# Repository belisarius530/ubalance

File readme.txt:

This is the first of many files,
may they all be merry and bright -JF

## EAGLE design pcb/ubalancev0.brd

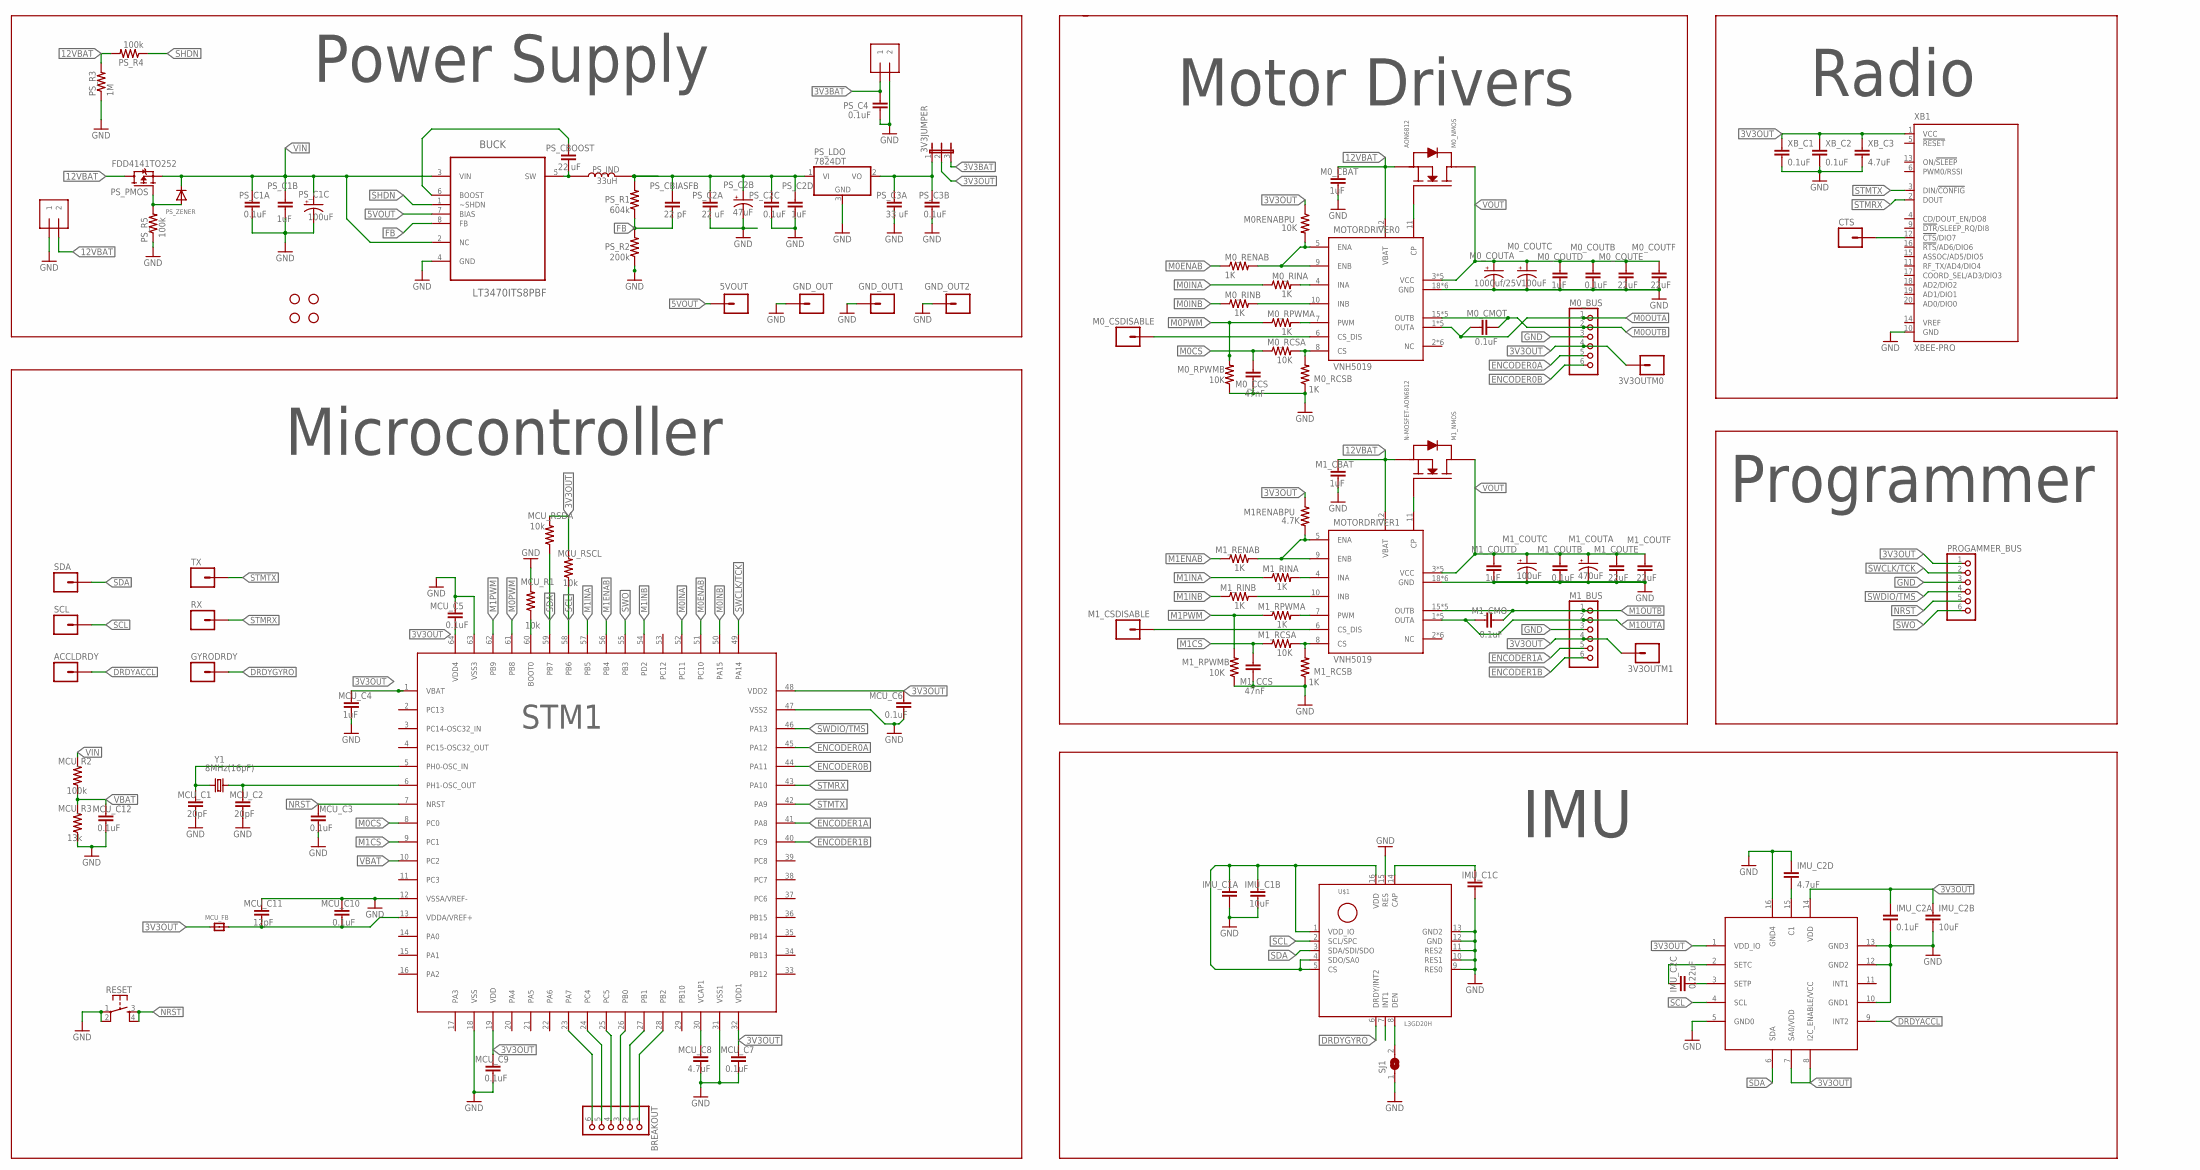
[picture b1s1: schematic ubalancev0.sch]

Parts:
3V3JUMPER: JUMPER3
3V3OUTM0, 3V3OUTM1, 5VOUT: M01PTH; 1X01
ACCLDRDY: M01PTH; 1X01
BREAKOUT: PINHD-1X6LOCK; 1X06-BIGLOCK
BUCK: LT3470ITS8PBF; SOT65P280X100-8N
CTS: M01PTH; 1X01
GND_OUT, GND_OUT1, GND_OUT2: M01PTH; 1X01
GYRODRDY: M01PTH; 1X01
IMU_C1A, IMU_C2A: 0.1uF; 0805
IMU_C1B, IMU_C2B: 10uF; 0805
IMU_C1C: 10nF; 0805
IMU_C2C: 0.22uF; 0805
IMU_C2D: 4.7uF; 0805
M0RENABPU, M0_RCSA, M0_RPWMB, M1_RCSA, M1_RPWMB: 10K; 0805
M0_BUS, M1_BUS: PINHD-1X6LOCK; 1X06-BIGLOCK
M0_CBAT, M0_COUTD, M1_CBAT, M1_COUTD: 1uF; 0805
M0_CCS, M1_CCS: 47nF; 0805
M0_CMOT, M0_COUTB, M1_CMO, M1_COUTB: 0.1uF; 0805
M0_COUTA: 1000uf/25V; CPOL-RADIAL-1000UF-25V-KIT
M0_COUTC, M1_COUTC: 100uF; PANASONIC_D
M0_COUTE, M1_COUTE, M1_COUTF: 22uF; 1206
M0_COUTF: 22uF; 0805
M0_CSDISABLE, M1_CSDISABLE: M01PTH; 1X01
M0_NMOS: AON6812; 8DFN-5*6MM
M0_RCSB, M0_RENAB, M0_RINA, M0_RINB, M0_RPWMA, M1_RCSB, M1_RENAB, M1_RINA, M1_RINB, M1_RPWMA: 1K; 0805
M1RENABPU: 4.7K; 0805
M1_COUTA: 470uF; PANASONIC_G
M1_NMOS: N-MOSFET-AON6812; 8DFN-5*6MM
MCU_C1, MCU_C2: 20pF; 0805
MCU_C3, MCU_C5, MCU_C6, MCU_C7, MCU_C9, MCU_C10, MCU_C12: 0.1uF; 0805
MCU_C4: 1uF; 0805
MCU_C8: 4.7uF; 0805
MCU_C11: 12pF; 0805
MCU_FB: FERRITE; 0603
MCU_R1: 10k; 0805
MCU_R2: 100k; 0805
MCU_R3: 13k; 0805
MCU_RSCL: 10k; 0805
MCU_RSDA: 10k; 0805
MOTORDRIVER0, MOTORDRIVER1: VNH5019; MULTIPOWERSO-30
PROGAMMER_BUS: PINHD-1X6LOCK; 1X06-BIGLOCK
PS_3V3TERM, PS_12VTERM: 1X2-3.5MM
PS_C1A, PS_C2C, PS_C3B, PS_C4: 0.1uF; 0805
PS_C1B, PS_C2D: 1uF; 0805
PS_C1C: 100uF; PANASONIC_D
PS_C2A: 22 uF; 1206
PS_C2B: 47uF; PANASONIC_D
PS_C3A: 33 uF; 1206
PS_CBIASFB: 22 pF; 0805
PS_CBOOST: .22 uF; 0402-CAP
PS_IND: 33uH; VLCF5024
PS_LDO: 7824DT; TO252
PS_PMOS: FDD4141TO252; TO252
PS_R1: 604k; 0805
PS_R2: 200k; 0805
PS_R3: 1M; 0805
PS_R4, PS_R5: 100k; 0805
PS_ZENER: DIODESOD-123; SOD-123
RESET: TAC_SWITCHPTH; TACTILE-PTH
RX: M01PTH; 1X01
SCL: M01PTH; 1X01
SDA: M01PTH; 1X01
SJ1: SOLDERJUMPER; SOLDERJUMPER_ARROW_NOPASTE
STANDOFF1, STANDOFF2, STANDOFF3, STANDOFF4: STAND-OFF
STM1: STM32F4; LQFP64
TX: M01PTH; 1X01
U$1: L3GD20H; LGA16_3X3MM
U$2: LSM303D; LGA16_3X3MM
XB1: XBEE-PRO
XB_C1, XB_C2: 0.1uF; 0805
XB_C3: 4.7uF; 0805
Y1: 8MHz(16pF); HC49US

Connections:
3V3BAT: 3V3JUMPER.3, PS_3V3TERM.1, PS_C4.1
3V3OUT: 3V3JUMPER.2, 3V3OUTM0.1, 3V3OUTM1.1, IMU_C1A.1, IMU_C1B.1, IMU_C2A.1, IMU_C2B.1, M0RENABPU.1, M0_BUS.4, M1RENABPU.1, M1_BUS.4, MCU_C4.1, MCU_C5.1, MCU_C6.2, MCU_C7.1, MCU_C9.1, MCU_FB.1, MCU_RSCL.2, MCU_RSDA.2, PROGAMMER_BUS.1, STM1.1 (VBAT), STM1.19 (VDD), STM1.32 (VDD1), STM1.48 (VDD2), STM1.64 (VDD4), U$1.1 (VDD_IO), U$1.4 (SDO/SA0), U$1.5 (CS), U$1.16 (VDD), U$2.1 (VDD_IO), U$2.7 (SA0/VDD), U$2.8 (I2C_ENABLE/VCC), U$2.14 (VDD), XB1.1 (VCC), XB_C1.1, XB_C2.1, XB_C3.1
3V3OUTREG: 3V3JUMPER.1, PS_C3A.1, PS_C3B.1, PS_LDO.2 (VO)
5VOUT: 5VOUT.1, BUCK.7 (BIAS), PS_C2A.1, PS_C2B.+, PS_C2C.1, PS_C2D.1, PS_CBIASFB.1, PS_IND.P2, PS_LDO.1 (VI), PS_R1.2
12VBAT: M0_CBAT.1, M0_NMOS.S1 (SOURCE), M0_NMOS.S2 (SOURCE), M0_NMOS.S3 (SOURCE), M1_CBAT.1, M1_NMOS.S1 (SOURCE), M1_NMOS.S2 (SOURCE), M1_NMOS.S3 (SOURCE), MOTORDRIVER0.12 (VBAT), MOTORDRIVER1.12 (VBAT), PS_12VTERM.2, PS_PMOS.3 (D), PS_R3.2, PS_R4.2
CAP: IMU_C1C.1, U$1.14 (CAP)
DRDYACCL: ACCLDRDY.1, U$2.9 (INT2)
DRDYGYRO: GYRODRDY.1, U$1.6 (DRDY/INT2)
ENCODER0A: M0_BUS.5, STM1.45 (PA12)
ENCODER0B: M0_BUS.6, STM1.44 (PA11)
ENCODER1A: M1_BUS.5, STM1.41 (PA8)
ENCODER1B: M1_BUS.6, STM1.40 (PC9)
FB: BUCK.8 (FB), PS_CBIASFB.2, PS_R1.1, PS_R2.2
GND: BUCK.4 (GND), GND_OUT.1, GND_OUT1.1, GND_OUT2.1, IMU_C1A.2, IMU_C1B.2, IMU_C1C.2, IMU_C2A.2, IMU_C2B.2, IMU_C2D.1, M0_BUS.3, M0_CBAT.2, M0_CCS.2, M0_COUTA.-, M0_COUTB.2, M0_COUTC.-, M0_COUTD.2, M0_COUTE.2, M0_COUTF.2, M0_RCSB.1, M0_RPWMB.1, M1_BUS.3, M1_CBAT.2, M1_CCS.2, M1_COUTA.-, M1_COUTB.2, M1_COUTC.-, M1_COUTD.2, M1_COUTE.2, M1_COUTF.2, M1_RCSB.1, M1_RPWMB.1, MCU_C1.2, MCU_C2.2, MCU_C3.2, MCU_C4.2, MCU_C5.2, MCU_C6.1, MCU_C7.2, MCU_C8.2, MCU_C9.2, MCU_C10.2, MCU_C11.1, MCU_C12.2, MCU_R1.2, MCU_R3.1, MOTORDRIVER0.18 (GND), MOTORDRIVER0.19 (GND), MOTORDRIVER0.20 (GND), MOTORDRIVER0.26 (GND), MOTORDRIVER0.27 (GND), MOTORDRIVER0.28 (GND), MOTORDRIVER1.18 (GND), MOTORDRIVER1.19 (GND), MOTORDRIVER1.20 (GND), MOTORDRIVER1.26 (GND), MOTORDRIVER1.27 (GND), MOTORDRIVER1.28 (GND), PROGAMMER_BUS.3, PS_3V3TERM.2, PS_12VTERM.1, PS_C1A.2, PS_C1B.2, PS_C1C.-, PS_C2A.2, PS_C2B.-, PS_C2C.2, PS_C2D.2, PS_C3A.2, PS_C3B.2, PS_C4.2, PS_LDO.3 (GND), PS_R2.1, PS_R3.1, PS_R5.1, RESET.1, RESET.2, SJ1.1, STM1.12 (VSSA/VREF-), STM1.18 (VSS), STM1.31 (VSS1), STM1.47 (VSS2), STM1.63 (VSS3), U$1.9 (RES0), U$1.10 (RES1), U$1.11 (RES2), U$1.12 (GND), U$1.13 (GND2), U$1.15 (RES), U$2.5 (GND0), U$2.10 (GND1), U$2.12 (GND2), U$2.13 (GND3), U$2.16 (GND4), XB1.10 (GND), XB_C1.2, XB_C2.2, XB_C3.2
M0CS: M0_CCS.1, M0_RCSA.1, STM1.8 (PC0)
M0ENAB: M0_RENAB.1, STM1.51 (PC10)
M0INA: M0_RINA.1, STM1.52 (PC11)
M0INB: M0_RINB.1, STM1.50 (PA15)
M0OUTA: M0_BUS.1, M0_CMOT.1, MOTORDRIVER0.1 (OUTA), MOTORDRIVER0.25 (OUTA), MOTORDRIVER0.30 (OUTA), MOTORDRIVER0.OUTA, MOTORDRIVER0.OUTA@1 (OUTA)
M0OUTB: M0_BUS.2, M0_CMOT.2, MOTORDRIVER0.15 (OUTB), MOTORDRIVER0.16 (OUTB), MOTORDRIVER0.21 (OUTB), MOTORDRIVER0.OUTB, MOTORDRIVER0.OUTB@1 (OUTB)
M0PWM: M0_RPWMA.1, M0_RPWMB.2, STM1.61 (PB8)
M1CS: M1_CCS.1, M1_RCSA.1, STM1.9 (PC1)
M1ENAB: M1_RENAB.1, STM1.56 (PB4)
M1INA: M1_RINA.1, STM1.57 (PB5)
M1INB: M1_RINB.1, STM1.54 (PD2)
M1OUTA: M1_BUS.2, M1_CMO.1, MOTORDRIVER1.1 (OUTA), MOTORDRIVER1.25 (OUTA), MOTORDRIVER1.30 (OUTA), MOTORDRIVER1.OUTA, MOTORDRIVER1.OUTA@1 (OUTA)
M1OUTB: M1_BUS.1, M1_CMO.2, MOTORDRIVER1.15 (OUTB), MOTORDRIVER1.16 (OUTB), MOTORDRIVER1.21 (OUTB), MOTORDRIVER1.OUTB, MOTORDRIVER1.OUTB@1 (OUTB)
M1PWM: M1_RPWMA.1, M1_RPWMB.2, STM1.62 (PB9)
unnamed: M1_NMOS.G (GATE), MOTORDRIVER1.11 (CP)
unnamed: BUCK.6 (BOOST), PS_CBOOST.1
unnamed: M0_NMOS.G (GATE), MOTORDRIVER0.11 (CP)
unnamed: IMU_C2C.1, U$2.3 (SETP)
unnamed: BREAKOUT.6, STM1.23 (PA7)
unnamed: M0RENABPU.2, M0_RENAB.2, MOTORDRIVER0.5 (ENA), MOTORDRIVER0.9 (ENB)
unnamed: MCU_C10.1, MCU_C11.2, MCU_FB.2, STM1.13 (VDDA/VREF+)
unnamed: BREAKOUT.5, STM1.24 (PC4)
unnamed: M0_RINA.2, MOTORDRIVER0.4 (INA)
unnamed: M0_RINB.2, MOTORDRIVER0.10 (INB)
unnamed: M0_RPWMA.2, MOTORDRIVER0.7 (PWM)
unnamed: M0_CSDISABLE.1, MOTORDRIVER0.6 (CS_DIS)
unnamed: M0_RCSA.2, M0_RCSB.2, MOTORDRIVER0.8 (CS)
unnamed: MCU_C8.1, STM1.30 (VCAP1)
unnamed: MCU_R1.1, STM1.60 (BOOT0)
unnamed: IMU_C2D.2, U$2.15 (C1)
unnamed: IMU_C2C.2, U$2.2 (SETC)
unnamed: BREAKOUT.4, STM1.25 (PC5)
unnamed: M1RENABPU.2, M1_RENAB.2, MOTORDRIVER1.5 (ENA), MOTORDRIVER1.9 (ENB)
unnamed: M1_RINA.2, MOTORDRIVER1.4 (INA)
unnamed: M1_RINB.2, MOTORDRIVER1.10 (INB)
unnamed: M1_RPWMA.2, MOTORDRIVER1.7 (PWM)
unnamed: M1_CSDISABLE.1, MOTORDRIVER1.6 (CS_DIS)
unnamed: M1_RCSA.2, M1_RCSB.2, MOTORDRIVER1.8 (CS)
unnamed: BREAKOUT.3, STM1.26 (PB0)
unnamed: MCU_C1.1, STM1.5 (PH0-OSC_IN), Y1.1
unnamed: MCU_C2.1, STM1.6 (PH1-OSC_OUT), Y1.2
unnamed: BREAKOUT.2, STM1.27 (PB1)
unnamed: BREAKOUT.1, STM1.28 (PB2)
unnamed: SJ1.2, U$1.8 (DEN)
unnamed: CTS.1, XB1.12 (!CTS!/DIO7)
NRST: MCU_C3.1, PROGAMMER_BUS.5, RESET.3, RESET.4, STM1.7 (NRST)
PMOSGATE: PS_PMOS.1 (G), PS_R5.2, PS_ZENER.A
SCL: MCU_RSCL.1, SCL.1, STM1.58 (PB6), U$1.2 (SCL/SPC), U$2.4 (SCL)
SDA: MCU_RSDA.1, SDA.1, STM1.59 (PB7), U$1.3 (SDA/SDI/SDO), U$2.6 (SDA)
SHDN: BUCK.1 (~SHDN), PS_R4.1
STMRX: RX.1, STM1.43 (PA10), XB1.2 (DOUT)
STMTX: STM1.42 (PA9), TX.1, XB1.3 (DIN/!CONFIG)
SW: BUCK.5 (SW), PS_CBOOST.2, PS_IND.P1
SWCLK/TCK: PROGAMMER_BUS.2, STM1.49 (PA14)
SWDIO/TMS: PROGAMMER_BUS.4, STM1.46 (PA13)
SWO: PROGAMMER_BUS.6, STM1.55 (PB3)
VBAT: MCU_C12.1, MCU_R2.1, MCU_R3.2, STM1.10 (PC2)
VIN: BUCK.2 (NC), BUCK.3 (VIN), MCU_R2.2, PS_C1A.1, PS_C1B.1, PS_C1C.+, PS_PMOS.2 (S), PS_ZENER.C
VOUT: M0_COUTA.+, M0_COUTB.1, M0_COUTC.+, M0_COUTD.1, M0_COUTE.1, M0_COUTF.1, M0_NMOS.D1 (DRAIN), M0_NMOS.D2 (DRAIN), M0_NMOS.D3 (DRAIN), M0_NMOS.D4 (DRAIN), M0_NMOS.D5 (DRAIN), M1_COUTA.+, M1_COUTB.1, M1_COUTC.+, M1_COUTD.1, M1_COUTE.1, M1_COUTF.1, M1_NMOS.D1 (DRAIN), M1_NMOS.D2 (DRAIN), M1_NMOS.D3 (DRAIN), M1_NMOS.D4 (DRAIN), M1_NMOS.D5 (DRAIN), MOTORDRIVER0.3 (VCC), MOTORDRIVER0.13 (VCC), MOTORDRIVER0.23 (VCC), MOTORDRIVER0.VCC, MOTORDRIVER0.VCC@1 (VCC), MOTORDRIVER1.3 (VCC), MOTORDRIVER1.13 (VCC), MOTORDRIVER1.23 (VCC), MOTORDRIVER1.VCC, MOTORDRIVER1.VCC@1 (VCC)

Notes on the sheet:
Microcontroller
Power Supply
Motor Drivers
Radio
IMU
Programmer

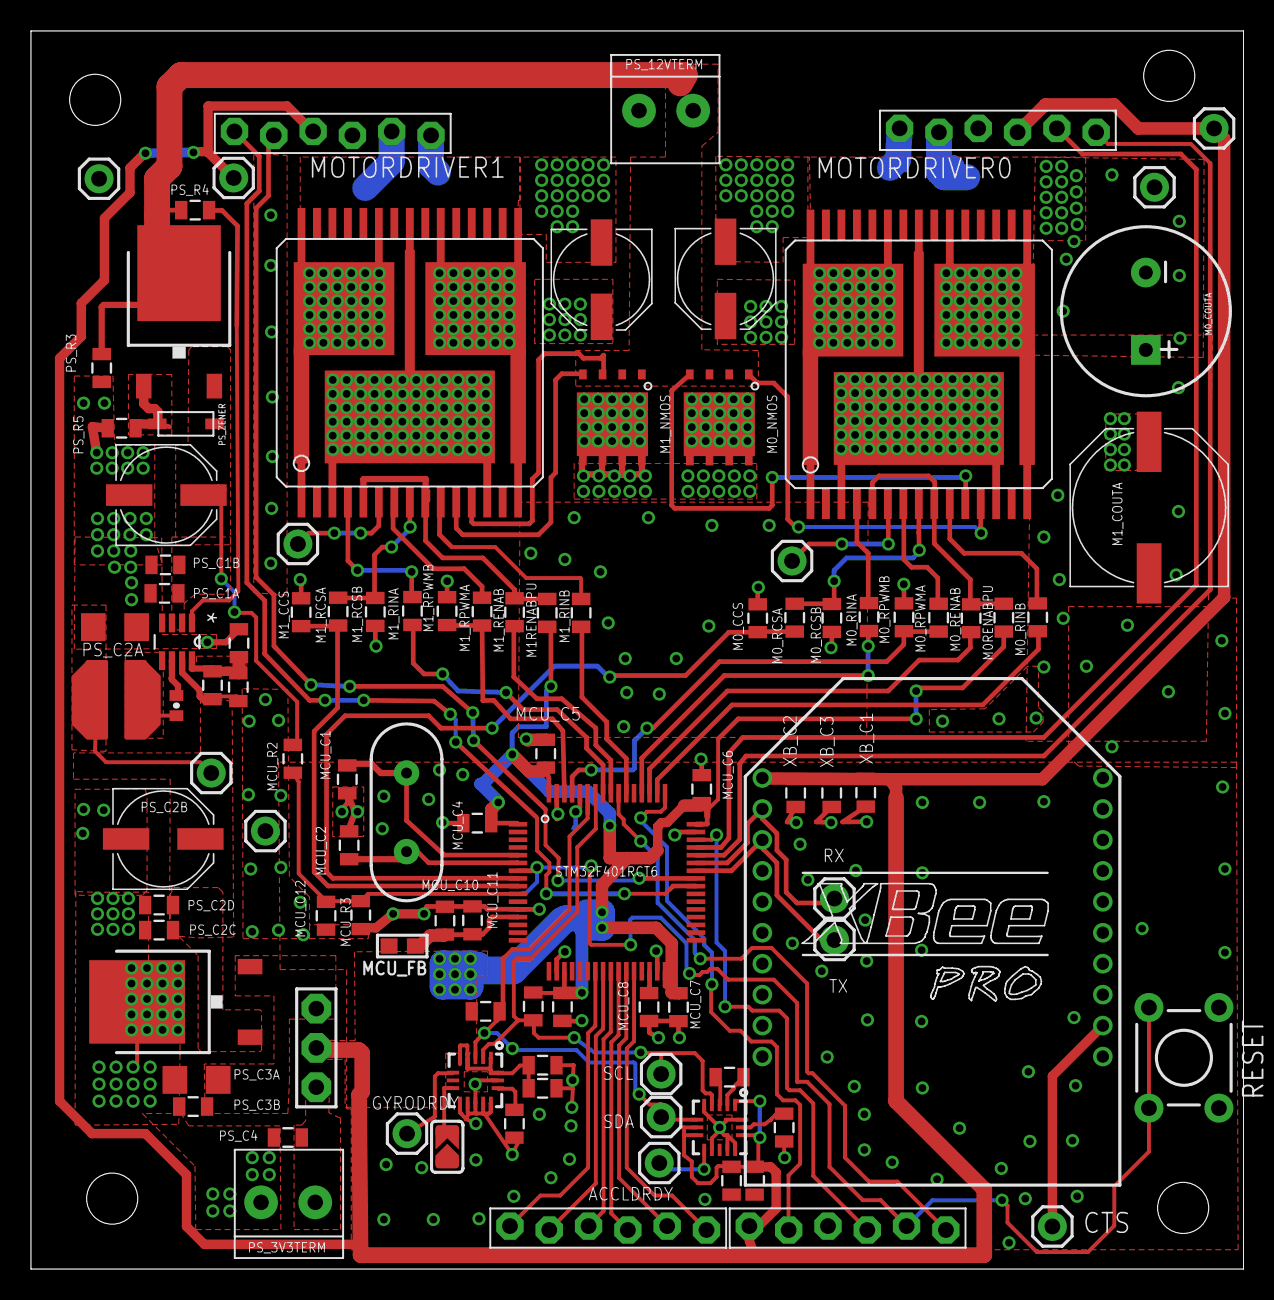
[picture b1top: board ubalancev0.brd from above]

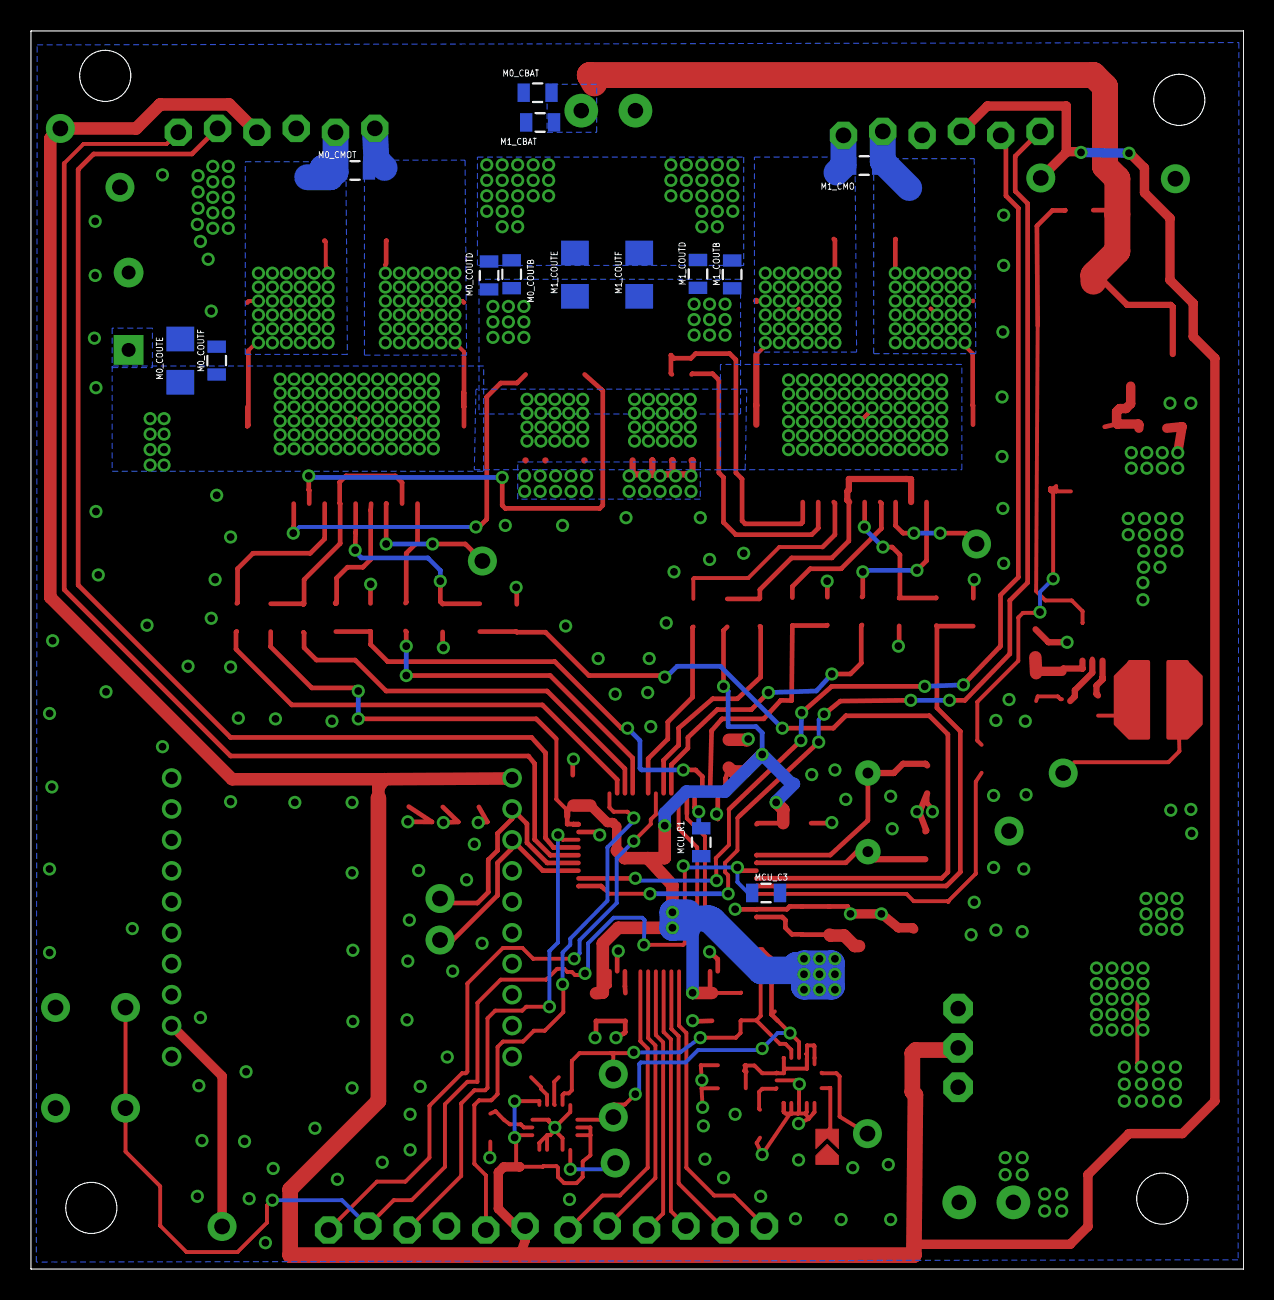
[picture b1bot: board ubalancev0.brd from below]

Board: 2 copper layers, 78.3 x 80.0 mm, 121 parts (14 on the bottom side), 73 nets.

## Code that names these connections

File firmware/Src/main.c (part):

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  __GPIOA_CLK_ENABLE();
  __GPIOB_CLK_ENABLE();

    /*Configure GPIO pins : PC9(ENCODER1B) */
    GPIO_InitStruct.Pin = GPIO_PIN_9;
    GPIO_InitStruct.Mode = GPIO_MODE_IT_RISING_FALLING;
    GPIO_InitStruct.Pull = GPIO_NOPULL;
    HAL_GPIO_Init(GPIOC, &GPIO_InitStruct);
        
    /*Configure GPIO pins : PA8(ENCODER1A) */
    GPIO_InitStruct.Pin = GPIO_PIN_8;
    GPIO_InitStruct.Mode = GPIO_MODE_IT_RISING_FALLING;
    GPIO_InitStruct.Pull = GPIO_NOPULL;
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    HAL_NVIC_SetPriority(EXTI9_5_IRQn, 5, 0);
    HAL_NVIC_EnableIRQ(EXTI9_5_IRQn);
    
    /*Configure GPIO pins : PA11(ENCODER0B), PA12(ENCODER0A) */
    GPIO_InitStruct.Pin = GPIO_PIN_11|GPIO_PIN_12;
    GPIO_InitStruct.Mode = GPIO_MODE_IT_RISING_FALLING;
    GPIO_InitStruct.Pull = GPIO_NOPULL;
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  GPIO_InitStruct.Alternate = GPIO_AF7_USART2;
  HAL_GPIO_Init(GPIOA, &GPIO_InitStruct);

  /*Configure GPIO pin : PA5(LED), PA15(M0INB) */
  GPIO_InitStruct.Pin = GPIO_PIN_5|GPIO_PIN_15;
  GPIO_InitStruct.Mode = GPIO_MODE_OUTPUT_PP;
  GPIO_InitStruct.Pull = GPIO_NOPULL;
  GPIO_InitStruct.Speed = GPIO_SPEED_LOW;
  HAL_GPIO_Init(GPIOA, &GPIO_InitStruct);
  
  /*Configure GPIO pins : PC10(M0ENAB) */
  GPIO_InitStruct.Pin = GPIO_PIN_10;
  GPIO_InitStruct.Mode = GPIO_MODE_INPUT;
  GPIO_InitStruct.Pull = GPIO_PULLUP;
  HAL_GPIO_Init(GPIOC, &GPIO_InitStruct);
  
  /*Configure GPIO pins : PC11(M0INA) */
  GPIO_InitStruct.Pin = GPIO_PIN_11;
  GPIO_InitStruct.Mode = GPIO_MODE_OUTPUT_PP;
  GPIO_InitStruct.Pull = GPIO_NOPULL;
  GPIO_InitStruct.Speed = GPIO_SPEED_LOW;
  HAL_GPIO_Init(GPIOC, &GPIO_InitStruct);
  
  /*Configure GPIO pins : PD2(M1INB) */
  GPIO_InitStruct.Pin = GPIO_PIN_2;
  GPIO_InitStruct.Mode = GPIO_MODE_OUTPUT_PP;
  GPIO_InitStruct.Pull = GPIO_NOPULL;
  GPIO_InitStruct.Speed = GPIO_SPEED_LOW;
  HAL_GPIO_Init(GPIOD, &GPIO_InitStruct);

  /*Configure GPIO pins : PB4(M1ENAB) */
  GPIO_InitStruct.Pin = GPIO_PIN_4;
  GPIO_InitStruct.Mode = GPIO_MODE_INPUT;
  GPIO_InitStruct.Pull = GPIO_PULLUP;
  HAL_GPIO_Init(GPIOB, &GPIO_InitStruct);
  
  /*Configure GPIO pins : PB5(M1INA) */
  GPIO_InitStruct.Pin = GPIO_PIN_5;
  GPIO_InitStruct.Mode = GPIO_MODE_OUTPUT_PP;
  GPIO_InitStruct.Pull = GPIO_NOPULL;
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
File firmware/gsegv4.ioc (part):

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Mcu.Name=STM32F401R(B-C-D-E)Tx
Mcu.Package=LQFP64
Mcu.UserName=STM32F401RETx
PA10.Mode=Asynchronous
PA10.Signal=USART1_RX
PA13.GPIOParameters=GPIO_Label
PA13.GPIO_Label=TMS
PA13.Mode=Trace-Asynchronous_SW
PA13.Signal=SYS_JTMS-SWDIO
PA14.GPIOParameters=GPIO_Label
PA14.GPIO_Label=TCK
PA14.Mode=Trace-Asynchronous_SW
PA14.Signal=SYS_JTCK-SWCLK
PA2.GPIOParameters=GPIO_Label,GPIO_Speed,GPIO_PuPd,GPIO_Mode
PA2.GPIO_Label=USART_TX
PA2.GPIO_Mode=GPIO_MODE_AF_PP
PA2.GPIO_PuPd=GPIO_NOPULL
PA2.GPIO_Speed=GPIO_SPEED_LOW
PA2.Signal=USART2_TX
PA3.GPIOParameters=GPIO_Label,GPIO_Speed,GPIO_PuPd,GPIO_Mode
PA3.GPIO_Label=USART_RX
PA3.GPIO_Mode=GPIO_MODE_AF_PP
PA3.GPIO_PuPd=GPIO_NOPULL
PA3.GPIO_Speed=GPIO_SPEED_LOW
PA3.Signal=USART2_RX
PA5.GPIOParameters=GPIO_ModeDefaultOutputPP,GPIO_Label,GPIO_Speed,GPIO_PuPd,GPIO_Mode
PA5.GPIO_Label=LD2 [Green Led]
PA5.GPIO_Mode=GPIO_MODE_OUTPUT_PP
PA5.GPIO_ModeDefaultOutputPP=GPIO_MODE_OUTPUT_PP
PA5.GPIO_PuPd=GPIO_NOPULL
PA5.GPIO_Speed=GPIO_SPEED_LOW
PA5.Signal=GPIO_Output
PA9.Mode=Asynchronous
PA9.Signal=USART1_TX
PB3.GPIOParameters=GPIO_Label
PB3.GPIO_Label=SWO
PB3.Mode=Trace-Asynchronous_SW
PB3.Signal=SYS_JTDO-SWO
PB6.Mode=I2C
PB6.Signal=I2C1_SCL
PB7.Mode=I2C
PB7.Signal=I2C1_SDA
PB8.Signal=S_TIM10_CH1
PB9.Signal=S_TIM11_CH1
PC0.Signal=ADCx_IN10
PC1.Signal=ADCx_IN11
PC13-ANTI_TAMP.GPIOParameters=GPIO_Label,GPIO_ModeDefaultEXTI,GPIO_PuPd
PC13-ANTI_TAMP.GPIO_Label=B1 [Blue PushButton]
PC13-ANTI_TAMP.GPIO_ModeDefaultEXTI=GPIO_MODE_EVT_RISING
PC13-ANTI_TAMP.GPIO_PuPd=GPIO_NOPULL
PC13-ANTI_TAMP.Signal=GPXTI13
PC14-OSC32_IN.Signal=RCC_OSC32_IN
PC15-OSC32_OUT.Signal=RCC_OSC32_OUT
PC2.Signal=ADCx_IN12
PH0\ -\ OSC_IN.Signal=RCC_OSC_IN
PH1\ -\ OSC_OUT.Signal=RCC_OSC_OUT
RCC.HSE_VALUE=8000000
RCC.SYSCLKFreq_VALUE=84000000
RCC.SYSCLKSource=RCC_SYSCLKSOURCE_PLLCLK
boardIOC=true

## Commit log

2015-09-01 Maiden Commit
2015-09-02 more git experimentation
2015-09-03 First serious commit
2015-09-03 added laser chasis design files
2015-09-03 removed fake file
2015-09-05 Commented task_control
2015-09-05 added more comments
2015-09-07 more comments added
2015-09-07 yet more comments
2015-09-16 implemented offset_angle algorithm
2015-09-16 refined angle offset algorithm
2015-09-17 added python interface scripts

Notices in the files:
firmware/Src/main.c:
COPYRIGHT(c) 2015 STMicroelectronics
(C) COPYRIGHT STMicroelectronics *****END OF FILE
parts and their libraries:
SparkFun-Passives: Licensing: Creative Commons ShareAlike 4.0 International - https://creativecommons.org/licenses/by-sa/4.0
microbuilder: This work is placed in the public domain, and may be freely used for commercial and non-commercial work with the following conditions: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
